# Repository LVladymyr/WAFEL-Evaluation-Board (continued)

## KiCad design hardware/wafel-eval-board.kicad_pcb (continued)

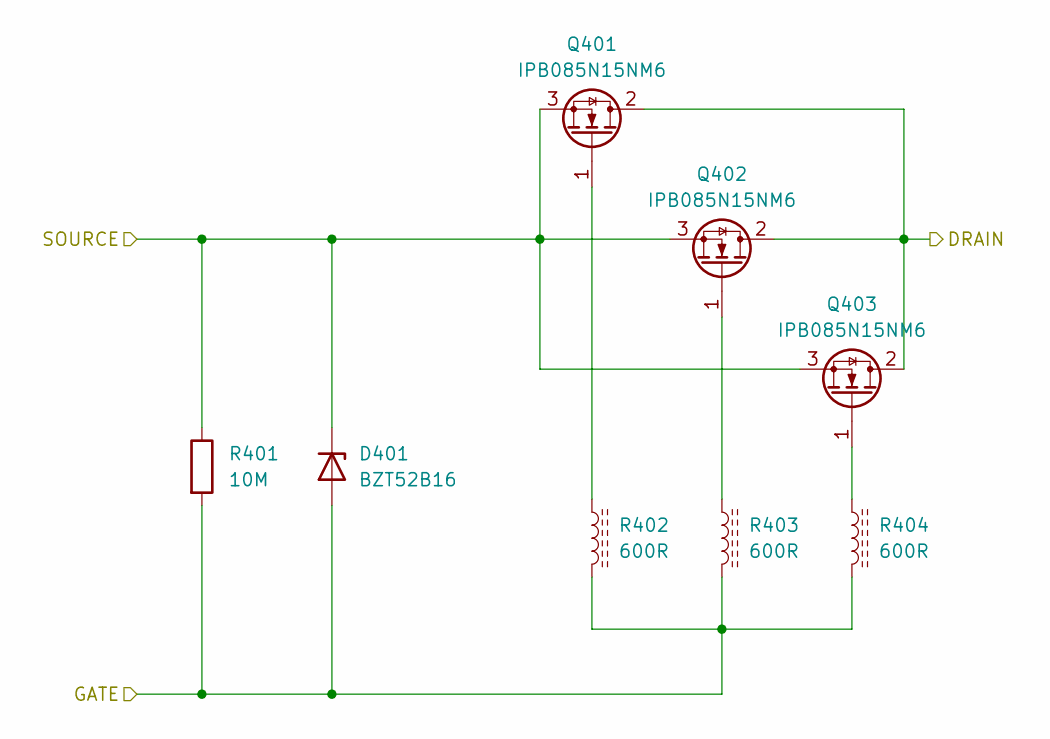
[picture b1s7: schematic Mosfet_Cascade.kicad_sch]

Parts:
D401: BZT52B16; D_SOD-123F
Q401, Q402, Q403: IPB085N15NM6; TO-263-2
R401: 10M; R_0603_1608Metric
R402, R403, R404: 600R; R_0603_1608Metric; LCSC C139183

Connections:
/BAT+: D401.1 (K), Q401.3 (S), Q402.3 (S), Q403.3 (S), R401.1; also elsewhere on the board
/High-Side N-MOSFET/MOSFET-CASCADE-CHG/DRAIN: Q401.2 (D), Q402.2 (D), Q403.2 (D); also elsewhere on the board
/High-Side N-MOSFET/MOSFET-CASCADE-CHG/GATE: D401.2 (A), R401.2, R402.2, R403.2, R404.2; also elsewhere on the board
unnamed: Q401.1 (G), R402.1
unnamed: Q402.1 (G), R403.1
unnamed: Q403.1 (G), R404.1

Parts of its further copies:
D501: BZT52B16; D_SOD-123F
Q501, Q502, Q503: IPB085N15NM6; TO-263-2
R501: 10M; R_0603_1608Metric
R502, R503, R504: 600R; R_0603_1608Metric; LCSC C139183

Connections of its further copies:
/High-Side N-MOSFET/MOSFET-CASCADE-CHG/DRAIN: Q501.2 (D), Q502.2 (D), Q503.2 (D); also elsewhere on the board
/High-Side N-MOSFET/MOSFET-CASCADE-DSG/GATE: D501.2 (A), R501.2, R502.2, R503.2, R504.2; also elsewhere on the board
/PACK+: D501.1 (K), Q501.3 (S), Q502.3 (S), Q503.3 (S), R501.1; also elsewhere on the board
unnamed: Q501.1 (G), R502.1
unnamed: Q502.1 (G), R503.1
unnamed: Q503.1 (G), R504.1

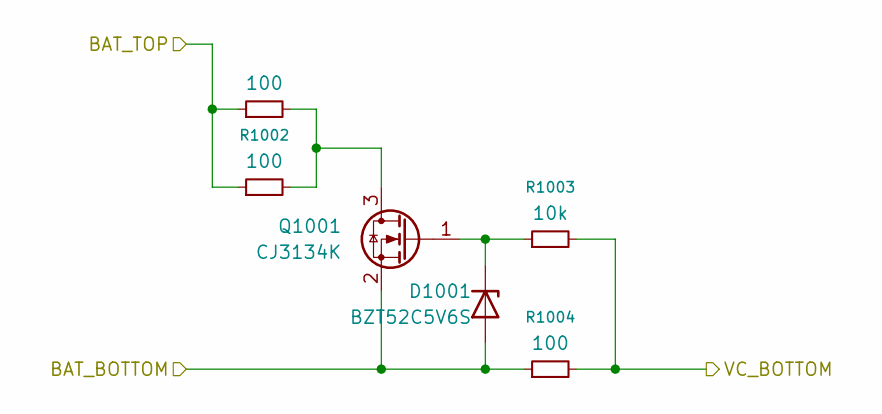
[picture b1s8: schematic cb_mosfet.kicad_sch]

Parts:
D1001: BZT52C5V6S; D_SOD-323; LCSC C19077441
Q1001: CJ3134K; SOT-723; LCSC C460977
R1001, R1002: 100; R_1206_3216Metric; LCSC C17901
R1003: 10k; R_0603_1608Metric; LCSC C25804
R1004: 100; R_0603_1608Metric; LCSC C22775

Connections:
/CB Mosfets/CELL0: D1001.2 (A), Q1001.2 (S), R1004.1; also elsewhere on the board
/CB Mosfets/CELL1: R1001.1, R1002.1; also elsewhere on the board
/CB Mosfets/VC0: R1003.2, R1004.2; also elsewhere on the board
unnamed: D1001.1 (K), Q1001.1 (G), R1003.1
unnamed: Q1001.3 (D), R1001.2, R1002.2

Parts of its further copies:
D1101, D1201, D1301, D1401, D1501, D1601, D1701, D1801, D1901: BZT52C5V6S; D_SOD-323; LCSC C19077441
Q1101, Q1201, Q1301, Q1401, Q1501, Q1601, Q1701, Q1801, Q1901: CJ3134K; SOT-723; LCSC C460977
R1101, R1102, R1201, R1202, R1301, R1302, R1401, R1402, R1501, R1502, R1601, R1602, R1701, R1702, R1801, R1802, R1901, R1902: 100; R_1206_3216Metric; LCSC C17901
R1103, R1203, R1303, R1403, R1503, R1603, R1703, R1803, R1903: 10k; R_0603_1608Metric; LCSC C25804
R1104, R1204, R1304, R1404, R1504, R1604, R1704, R1804, R1904: 100; R_0603_1608Metric; LCSC C22775

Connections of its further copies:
/CB Mosfets/CELL1: D1101.2 (A), Q1101.2 (S), R1104.1; also elsewhere on the board
/CB Mosfets/CELL2: D1201.2 (A), Q1201.2 (S), R1101.1, R1102.1, R1204.1; also elsewhere on the board
/CB Mosfets/CELL3: D1301.2 (A), Q1301.2 (S), R1201.1, R1202.1, R1304.1; also elsewhere on the board
/CB Mosfets/CELL4: D1401.2 (A), Q1401.2 (S), R1301.1, R1302.1, R1404.1; also elsewhere on the board
/CB Mosfets/CELL5: D1501.2 (A), Q1501.2 (S), R1401.1, R1402.1, R1504.1; also elsewhere on the board
/CB Mosfets/CELL6: D1601.2 (A), Q1601.2 (S), R1501.1, R1502.1, R1604.1; also elsewhere on the board
/CB Mosfets/CELL7: D1701.2 (A), Q1701.2 (S), R1601.1, R1602.1, R1704.1; also elsewhere on the board
/CB Mosfets/CELL8: D1801.2 (A), Q1801.2 (S), R1701.1, R1702.1, R1804.1; also elsewhere on the board
/CB Mosfets/CELL9: D1901.2 (A), Q1901.2 (S), R1801.1, R1802.1, R1904.1; also elsewhere on the board
/CB Mosfets/CELL10: R1901.1, R1902.1; also elsewhere on the board
/CB Mosfets/VC1: R1103.2, R1104.2; also elsewhere on the board
/CB Mosfets/VC2: R1203.2, R1204.2; also elsewhere on the board
/CB Mosfets/VC3: R1303.2, R1304.2; also elsewhere on the board
/CB Mosfets/VC4: R1403.2, R1404.2; also elsewhere on the board
/CB Mosfets/VC5: R1503.2, R1504.2; also elsewhere on the board
/CB Mosfets/VC6: R1603.2, R1604.2; also elsewhere on the board
/CB Mosfets/VC7: R1703.2, R1704.2; also elsewhere on the board
/CB Mosfets/VC8: R1803.2, R1804.2; also elsewhere on the board
/CB Mosfets/VC9: R1903.2, R1904.2; also elsewhere on the board
unnamed: D1101.1 (K), Q1101.1 (G), R1103.1
unnamed: D1201.1 (K), Q1201.1 (G), R1203.1
unnamed: D1301.1 (K), Q1301.1 (G), R1303.1
unnamed: D1401.1 (K), Q1401.1 (G), R1403.1
unnamed: D1501.1 (K), Q1501.1 (G), R1503.1
unnamed: D1601.1 (K), Q1601.1 (G), R1603.1
unnamed: D1701.1 (K), Q1701.1 (G), R1703.1
unnamed: D1801.1 (K), Q1801.1 (G), R1803.1
unnamed: D1901.1 (K), Q1901.1 (G), R1903.1
unnamed: Q1101.3 (D), R1101.2, R1102.2
unnamed: Q1201.3 (D), R1201.2, R1202.2
unnamed: Q1301.3 (D), R1301.2, R1302.2
unnamed: Q1401.3 (D), R1401.2, R1402.2
unnamed: Q1501.3 (D), R1501.2, R1502.2
unnamed: Q1601.3 (D), R1601.2, R1602.2
unnamed: Q1701.3 (D), R1701.2, R1702.2
unnamed: Q1801.3 (D), R1801.2, R1802.2
unnamed: Q1901.3 (D), R1901.2, R1902.2

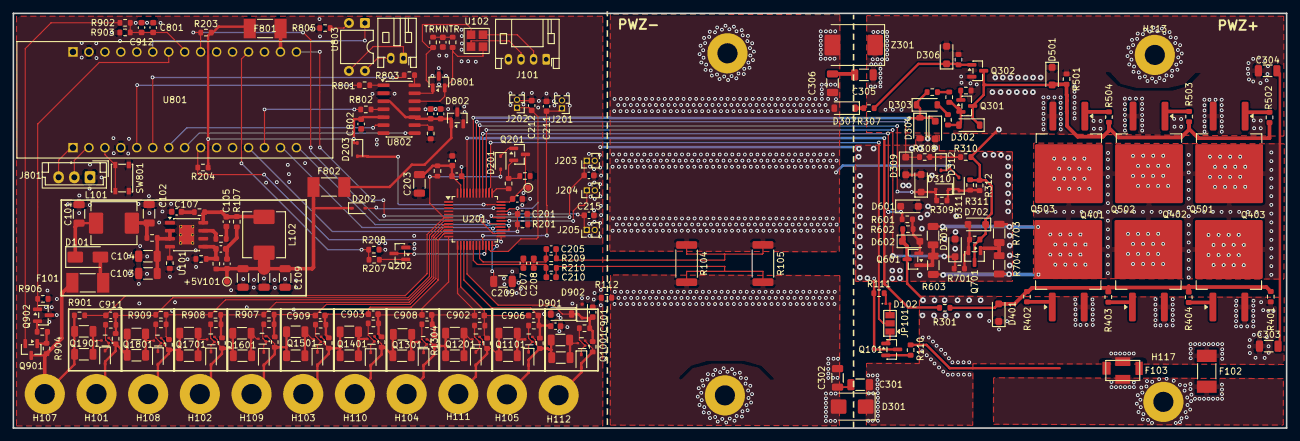
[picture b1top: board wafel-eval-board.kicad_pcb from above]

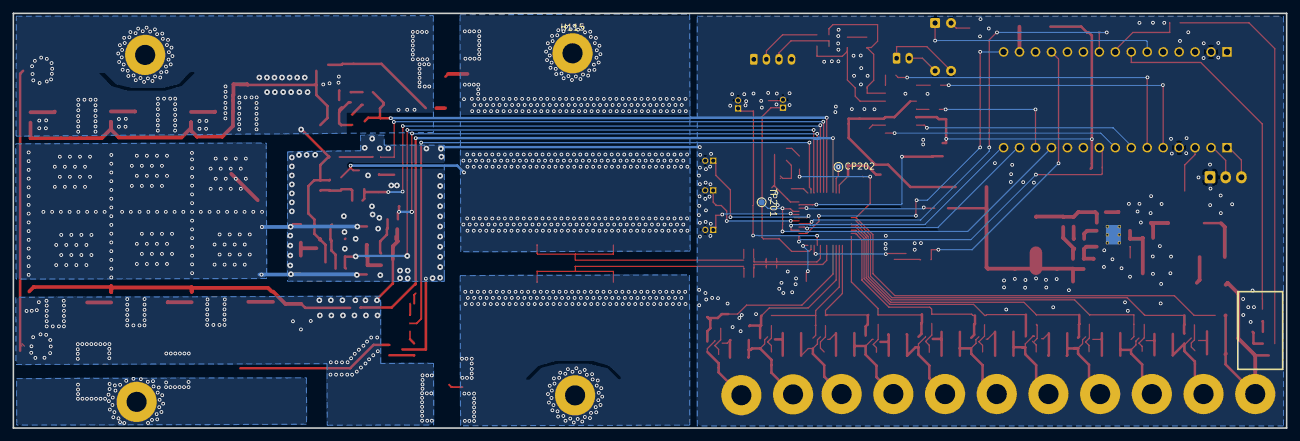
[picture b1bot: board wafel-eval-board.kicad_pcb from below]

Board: 2 copper layers, 202.6 x 66.0 mm, 256 parts (3 on the bottom side), 150 nets.

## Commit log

2026-03-20 Initial release v0.0.1
2026-03-20 fix: split 3D STEP export into separate non-fatal step
2026-03-20 fix: use run_by_default to isolate 3D STEP export
2026-04-03 add sync folder
2026-04-06 Restore robust hardware project state and clean up test files
2026-04-07 add fuses
2026-04-07 improve fuse connectios
2026-04-09 remove jetbrains mcps, add uv in home and update flake
2026-04-09 remove EN
2026-04-09 change props
2026-04-09 change add thermoprotection
2026-04-09 change change n transistor symbol
2026-04-09 hide symbols
2026-04-09 cleanup
2026-04-09 fix SPI pins
2026-04-10 fixes
2026-04-10 add bat{en adc}
2026-04-10 simplify page
2026-04-10 switch capasitors to 220mf
2026-04-13 improve can
2026-04-14 fix MCU pin mapping and resolve ERC conflicts
2026-04-14 use bus alias
2026-04-14 remove trash
2026-04-14 fix ERC warnings and footprint issues
2026-04-14 update schematics
2026-04-14 fix remaining missing footprints
2026-04-14 fix footprint strings inside embedded symbol definitions
2026-04-14 remove unconnected wire segment from frontend sheet
2026-04-14 first layout
2026-04-15 placed c mosfet
2026-04-17 reduced BOM
2026-04-17 increased size two times
2026-04-17 ADD ZONES
2026-04-17 Actualize resistors size
2026-04-18 some chnages
2026-04-18 added qulon zone
2026-04-19 Update C301-C306 to 1206 100V capacitors
2026-04-19 Replace gate resistors with ferrite beads (600R @ 100MHz)
2026-04-19 Docs: Update MOSFET protection with Ferrite Beads calculation
2026-04-19 Replace pre-charge/discharge MOSFETs with smaller 100V SOT-23 PJM10H01PSA
2026-04-19 Sync PCB layout with updated schematic footprints (Q601/Q701 to SOT-23, C301-C306 to 1206)
2026-04-19 Shrink load dump Schottky diodes to SOD-323 (BAT46WS)
2026-04-19 Manually replace gate resistors with ferrite bead symbols in schematics
2026-04-19 Sync PCB layout with updated gate ferrite bead symbols
2026-04-20 Replace huge SolderWire footprint with standard 2.54mm PinHeader
2026-04-20 Replace huge SS110 SMA diode (D201) with smaller B110WS in SOD-323
2026-04-20 Replace CAN TVS D802 (NUP2105L) with PESD1CAN
2026-04-20 Sync PCB layout with updated 2.54mm PinHeader footprints
2026-04-21 29 drc errors
2026-04-21 rm drc_report.txt
2026-04-21 move controll signals to back
2026-04-22 done 0001
2026-04-22 no 199 warns
2026-04-22 no 88 warns
2026-04-22 no 122 warns
2026-04-22 no 70 warns
2026-04-22 no 79 warns
2026-04-22 add thermal vias
2026-04-22 kelvin connect
2026-04-23 fix tracks of correct resistors
2026-05-01 small improvements
2026-05-01 add pdfs
